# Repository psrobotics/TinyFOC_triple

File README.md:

# TinyFOC_triple

<br> <br>
<br> <br>

* Compact 3 channel brushless motor driver with external encoder
* Supports I2C (AS5600) or AB (TLE5012B) encoders
* Hardwarer CAN, serial, SPI interface
* Input voltage: 9v - 24v, maximum phase current 1.5A
* 4 layer board / FR4 / 1.0mm thickness
* [SimpleFOC](https://github.com/simplefoc) compatible

Design file exported with [Autodesk EAGLE](https://www.autodesk.com/products/eagle/overview?term=1-YEAR&tab=subscription)

## ICs
* MCU [STM32F446RET6](https://www.st.com/en/microcontrollers-microprocessors/stm32f446re.html)
* Motor driver [DRV8313](https://www.ti.com/product/DRV8313?utm_source=google&utm_medium=cpc&utm_campaign=asc-null-null-GPN_EN-cpc-pf-google-wwe&utm_content=DRV8313&ds_k=DRV8313&DCM=yes&gclid=EAIaIQobChMIroSGo5PH_gIV7TatBh0lfQ1tEAAYASAAEgJeRvD_BwE&gclsrc=aw.ds) or [MS8313](https://www.lcsc.com/product-detail/Others_Hangzhou-Ruimeng-Tech-MS8313_C231942.html)
* Encoder [AS5600](https://ams.com/en/as5600) or [TLE5012B E1000](https://www.infineon.com/cms/en/product/sensor/magnetic-sensors/magnetic-position-sensors/angle-sensors/tle5012b-e1000/)

## Pin Out
<br> <br>

## License
MIT License

## Contact
* Shuang Peng, {shuangpe}@usc.edu

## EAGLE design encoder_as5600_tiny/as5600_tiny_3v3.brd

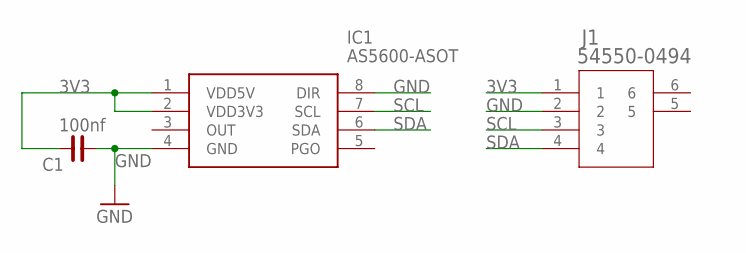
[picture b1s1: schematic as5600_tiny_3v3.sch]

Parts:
C1: 100nf; C0603
IC1: AS5600-ASOT; SOIC127P600X175-8N
J1: 54550-0494; CON4_1X4_DRB2_MOL

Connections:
3V3: C1.2, IC1.1 (VDD5V), IC1.2 (VDD3V3), J1.1
GND: C1.1, IC1.4 (GND), IC1.8 (DIR), J1.2
SCL: IC1.7 (SCL), J1.3
SDA: IC1.6 (SDA), J1.4

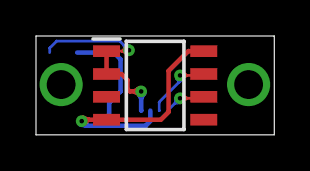
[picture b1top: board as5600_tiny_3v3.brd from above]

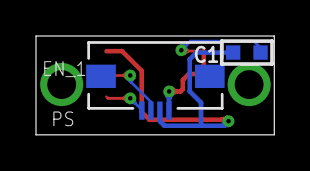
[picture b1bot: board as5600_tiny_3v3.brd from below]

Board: 2 copper layers, 13.2 x 5.5 mm, 3 parts (2 on the bottom side), 4 nets.

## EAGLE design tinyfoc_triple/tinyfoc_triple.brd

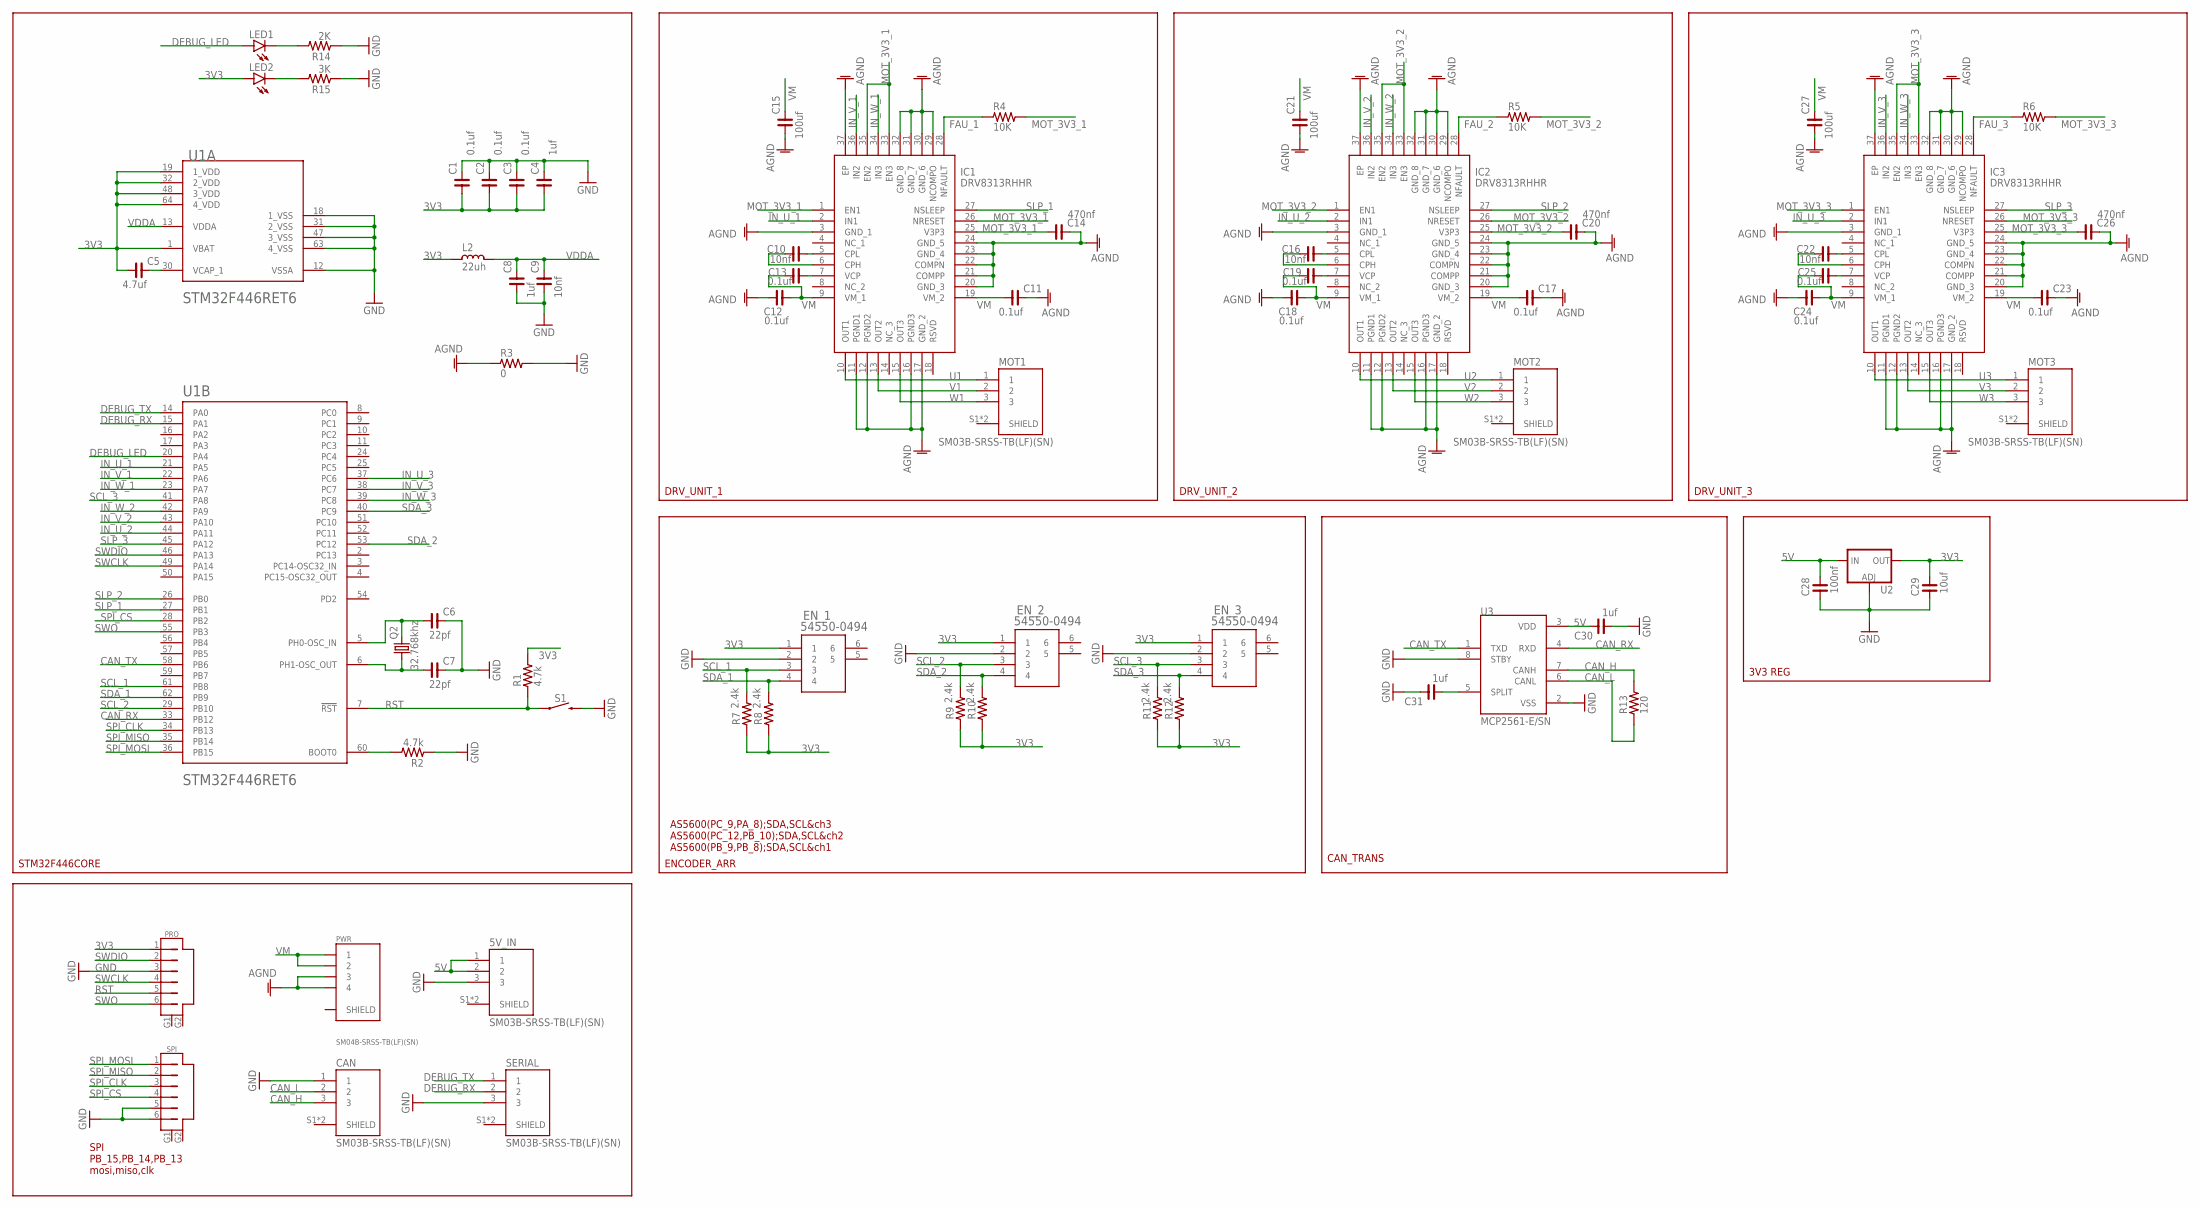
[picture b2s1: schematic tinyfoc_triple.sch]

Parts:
5V_IN: SM03B-SRSS-TB(LF)(SN); JST_SM03B-SRSS-TB(LF)(SN)
C1, C2, C3, C11, C12, C13, C17, C18, C19, C23, C24, C25: 0.1uf; C0603
C4, C8, C30, C31: 1uf; C0603
C5: 4.7uf; C1206
C6, C7: 22pf; C0603
C9, C10, C16, C22: 10nf; C0603
C14, C20, C26: 470nf; C0603
C15, C21, C27: 100uf; C1206
C28: 100nf; C0603
C29: 10uf; C0603
CAN: SM03B-SRSS-TB(LF)(SN); JST_SM03B-SRSS-TB(LF)(SN)
EN_1, EN_2, EN_3: 54550-0494; CON4_1X4_DRB2_MOL
IC1, IC2, IC3: DRV8313RHHR; QFN50P600X600X100-37N
L2: 22uh; PM0603
LED1, LED2: LEDCHIPLED_0603; CHIPLED_0603
MOT1, MOT2, MOT3: SM03B-SRSS-TB(LF)(SN); JST_SM03B-SRSS-TB(LF)(SN)
PRO: SM06B-SRSS-TB; SM06B
PWR: SM04B-SRSS-TB(LF)(SN); JST_SM04B-SRSS-TB(LF)(SN)
Q2: 32.768khz; 3.2X1.5
R1, R2: 4.7k; R0603
R3: 0; R0603
R4, R5, R6: 10K; R0603
R7, R8, R9, R10, R11, R12: 2.4k; R0603
R13: 120; R0603
R14: 2K; R0603
R15: 3K; R0603
S1: MOMENTARY-SWITCH-SPST-SMD-RIGHT-ANGLE; TACTILE_SWITCH_SMD_RIGHT_ANGLE
SERIAL: SM03B-SRSS-TB(LF)(SN); JST_SM03B-SRSS-TB(LF)(SN)
SPI: SM06B-SRSS-TB; SM06B
U1: STMICROELECTRONICS_STM32F446RET6STMICROELECTRONIC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; STMICROELECTRONICS_STM32F446RET6_0
U2: V_REG_LM1117SOT223; SOT223
U3: MCP2561-E/SN; SOIC127P600X175-8N

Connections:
3V3: C1.1, C2.1, C3.1, C4.1, C5.1, C29.2, EN_1.1, EN_2.1, EN_3.1, L2.2, LED2.A, PRO.1, R1.2, R7.1, R8.1, R9.1, R10.1, R11.1, R12.1, U1.1 (VBAT), U1.19 (1_VDD), U1.32 (2_VDD), U1.48 (3_VDD), U1.64 (4_VDD), U2.2 (OUT), U2.4 (OUT)
5V: 5V_IN.1, 5V_IN.2, C28.2, C30.2, U2.3 (IN), U3.3 (VDD)
AGND: C11.2, C12.1, C14.2, C15.1, C17.2, C18.1, C20.2, C21.1, C23.2, C24.1, C26.2, C27.1, IC1.3 (GND_1), IC1.11 (PGND1), IC1.12 (PGND2), IC1.16 (PGND3), IC1.17 (GND_2), IC1.20 (GND_3), IC1.21 (COMPP), IC1.22 (COMPN), IC1.23 (GND_4), IC1.24 (GND_5), IC1.29 (NCOMPO), IC1.30 (GND_6), IC1.31 (GND_7), IC1.32 (GND_8), IC1.37 (EP), IC2.3 (GND_1), IC2.11 (PGND1), IC2.12 (PGND2), IC2.16 (PGND3), IC2.17 (GND_2), IC2.20 (GND_3), IC2.21 (COMPP), IC2.22 (COMPN), IC2.23 (GND_4), IC2.24 (GND_5), IC2.29 (NCOMPO), IC2.30 (GND_6), IC2.31 (GND_7), IC2.32 (GND_8), IC2.37 (EP), IC3.3 (GND_1), IC3.11 (PGND1), IC3.12 (PGND2), IC3.16 (PGND3), IC3.17 (GND_2), IC3.20 (GND_3), IC3.21 (COMPP), IC3.22 (COMPN), IC3.23 (GND_4), IC3.24 (GND_5), IC3.29 (NCOMPO), IC3.30 (GND_6), IC3.31 (GND_7), IC3.32 (GND_8), IC3.37 (EP), PWR.3, PWR.4, R3.1
CAN_H: CAN.3, R13.2, U3.7 (CANH)
CAN_L: CAN.2, R13.1, U3.6 (CANL)
CAN_RX: U1.33 (PB12), U3.4 (RXD)
CAN_TX: U1.58 (PB6), U3.1 (TXD)
DEBUG_LED: LED1.A, U1.20 (PA4)
DEBUG_RX: SERIAL.2, U1.15 (PA1)
DEBUG_TX: SERIAL.1, U1.14 (PA0)
FAU_1: IC1.28 (NFAULT), R4.1
FAU_2: IC2.28 (NFAULT), R5.1
FAU_3: IC3.28 (NFAULT), R6.1
GND: 5V_IN.3, C1.2, C2.2, C3.2, C4.2, C6.2, C7.2, C8.1, C9.1, C28.1, C29.1, C30.1, C31.2, CAN.1, EN_1.2, EN_2.2, EN_3.2, PRO.3, R2.1, R3.2, R14.1, R15.1, S1.2, SERIAL.3, SPI.5, SPI.6, U1.12 (VSSA), U1.18 (1_VSS), U1.31 (2_VSS), U1.47 (3_VSS), U1.63 (4_VSS), U2.1 (ADJ), U3.2 (VSS), U3.8 (STBY)
IN_U_1: IC1.2 (IN1), U1.21 (PA5)
IN_U_2: IC2.2 (IN1), U1.44 (PA11)
IN_U_3: IC3.2 (IN1), U1.37 (PC6)
IN_V_1: IC1.36 (IN2), U1.22 (PA6)
IN_V_2: IC2.36 (IN2), U1.43 (PA10)
IN_V_3: IC3.36 (IN2), U1.38 (PC7)
IN_W_1: IC1.34 (IN3), U1.23 (PA7)
IN_W_2: IC2.34 (IN3), U1.42 (PA9)
IN_W_3: IC3.34 (IN3), U1.39 (PC8)
MOT_3V3_1: C14.1, IC1.1 (EN1), IC1.25 (V3P3), IC1.26 (NRESET), IC1.33 (EN3), IC1.35 (EN2), R4.2
MOT_3V3_2: C20.1, IC2.1 (EN1), IC2.25 (V3P3), IC2.26 (NRESET), IC2.33 (EN3), IC2.35 (EN2), R5.2
MOT_3V3_3: C26.1, IC3.1 (EN1), IC3.25 (V3P3), IC3.26 (NRESET), IC3.33 (EN3), IC3.35 (EN2), R6.2
unnamed: C5.2, U1.30 (VCAP_1)
unnamed: R2.2, U1.60 (BOOT0)
unnamed: C7.1, Q2.1, U1.6 (PH1-OSC_OUT)
unnamed: C10.2, IC1.5 (CPL)
unnamed: C6.1, Q2.2, U1.5 (PH0-OSC_IN)
unnamed: C10.1, IC1.6 (CPH)
unnamed: C13.2, IC1.7 (VCP)
unnamed: C16.2, IC2.5 (CPL)
unnamed: C16.1, IC2.6 (CPH)
unnamed: C19.2, IC2.7 (VCP)
unnamed: C22.2, IC3.5 (CPL)
unnamed: C22.1, IC3.6 (CPH)
unnamed: C25.2, IC3.7 (VCP)
unnamed: C31.1, U3.5 (SPLIT)
unnamed: LED2.C, R15.2
unnamed: LED1.C, R14.2
RST: PRO.5, R1.1, S1.1, U1.7 (!RST!)
SCL_1: EN_1.3, R7.2, U1.61 (PB8)
SCL_2: EN_2.3, R9.2, U1.29 (PB10)
SCL_3: EN_3.3, R11.2, U1.41 (PA8)
SDA_1: EN_1.4, R8.2, U1.62 (PB9)
SDA_2: EN_2.4, R10.2, U1.53 (PC12)
SDA_3: EN_3.4, R12.2, U1.40 (PC9)
SLP_1: IC1.27 (NSLEEP), U1.27 (PB1)
SLP_2: IC2.27 (NSLEEP), U1.26 (PB0)
SLP_3: IC3.27 (NSLEEP), U1.45 (PA12)
SPI_CLK: SPI.3, U1.34 (PB13)
SPI_CS: SPI.4, U1.28 (PB2)
SPI_MISO: SPI.2, U1.35 (PB14)
SPI_MOSI: SPI.1, U1.36 (PB15)
SWCLK: PRO.4, U1.49 (PA14)
SWDIO: PRO.2, U1.46 (PA13)
SWO: PRO.6, U1.55 (PB3)
U1: IC1.10 (OUT1), MOT1.1
U2: IC2.10 (OUT1), MOT2.1
U3: IC3.10 (OUT1), MOT3.1
V1: IC1.13 (OUT2), MOT1.2
V2: IC2.13 (OUT2), MOT2.2
V3: IC3.13 (OUT2), MOT3.2
VDDA: C8.2, C9.2, L2.1, U1.13 (VDDA)
VM: C11.1, C12.2, C13.1, C15.2, C17.1, C18.2, C19.1, C21.2, C23.1, C24.2, C25.1, C27.2, IC1.9 (VM_1), IC1.19 (VM_2), IC2.9 (VM_1), IC2.19 (VM_2), IC3.9 (VM_1), IC3.19 (VM_2), PWR.1, PWR.2
W1: IC1.15 (OUT3), MOT1.3
W2: IC2.15 (OUT3), MOT2.3
W3: IC3.15 (OUT3), MOT3.3

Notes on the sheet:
STM32F446CORE
DRV_UNIT_1
DRV_UNIT_2
DRV_UNIT_3
ENCODER_ARR
AS5600(PC_9,PA_8);SDA,SCL&ch3 AS5600(PC_12,PB_10);SDA,SCL&ch2 AS5600(PB_9,PB_8);SDA,SCL&ch1
SPI PB_15,PB_14,PB_13 mosi,miso,clk
3V3 REG
CAN_TRANS

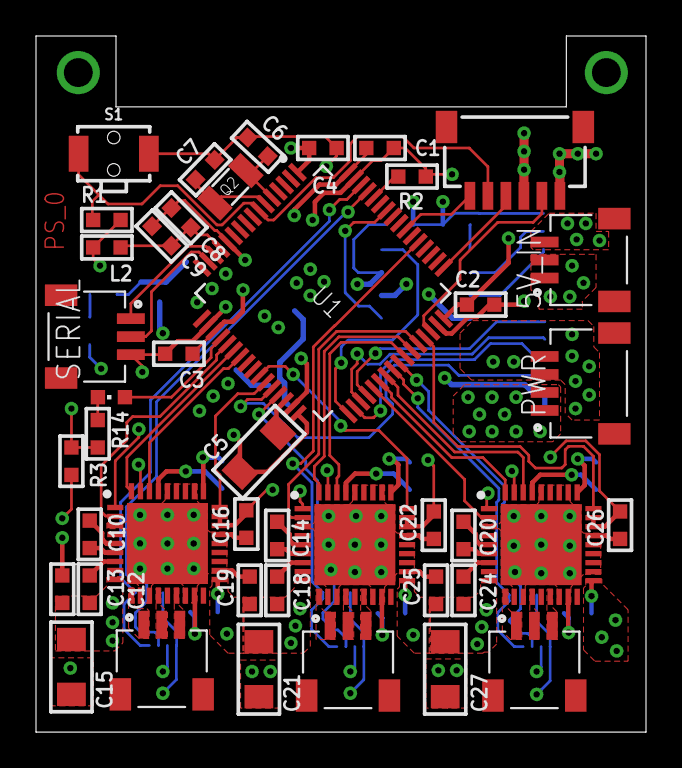
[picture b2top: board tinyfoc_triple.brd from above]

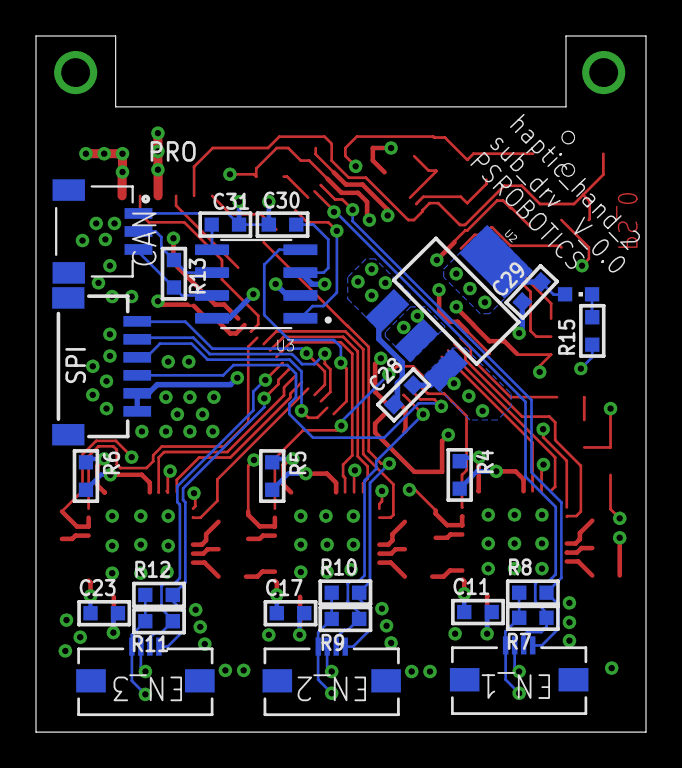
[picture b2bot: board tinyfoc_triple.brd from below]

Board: 4 copper layers, 33.9 x 38.7 mm, 69 parts (26 on the bottom side), 70 nets.

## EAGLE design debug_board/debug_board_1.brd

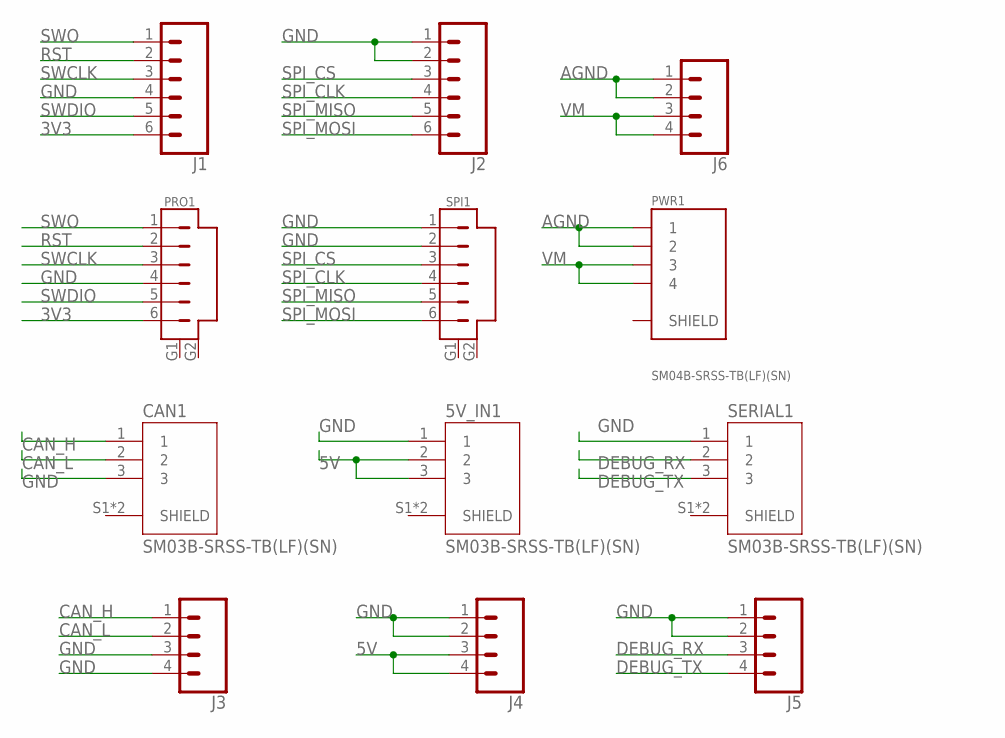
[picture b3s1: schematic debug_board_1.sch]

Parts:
5V_IN1: SM03B-SRSS-TB(LF)(SN); JST_SM03B-SRSS-TB(LF)(SN)
CAN1: SM03B-SRSS-TB(LF)(SN); JST_SM03B-SRSS-TB(LF)(SN)
J1, J2: CONN_06LONGPADS; 1X06_LONGPADS
J3, J4, J5, J6: CONN_04LONGPADS; 1X04_LONGPADS
PRO1: SM06B-SRSS-TB; SM06B
PWR1: SM04B-SRSS-TB(LF)(SN); JST_SM04B-SRSS-TB(LF)(SN)
SERIAL1: SM03B-SRSS-TB(LF)(SN); JST_SM03B-SRSS-TB(LF)(SN)
SPI1: SM06B-SRSS-TB; SM06B

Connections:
3V3: J1.6, PRO1.6
5V: 5V_IN1.2, 5V_IN1.3, J4.3, J4.4
AGND: J6.1, J6.2, PWR1.1, PWR1.2
CAN_H: CAN1.1, J3.1
CAN_L: CAN1.2, J3.2
DEBUG_RX: J5.3, SERIAL1.2
DEBUG_TX: J5.4, SERIAL1.3
GND: 5V_IN1.1, CAN1.3, J1.4, J2.1, J2.2, J3.3, J3.4, J4.1, J4.2, J5.1, J5.2, PRO1.4, SERIAL1.1, SPI1.1, SPI1.2
RST: J1.2, PRO1.2
SPI_CLK: J2.4, SPI1.4
SPI_CS: J2.3, SPI1.3
SPI_MISO: J2.5, SPI1.5
SPI_MOSI: J2.6, SPI1.6
SWCLK: J1.3, PRO1.3
SWDIO: J1.5, PRO1.5
SWO: J1.1, PRO1.1
VM: J6.3, J6.4, PWR1.3, PWR1.4

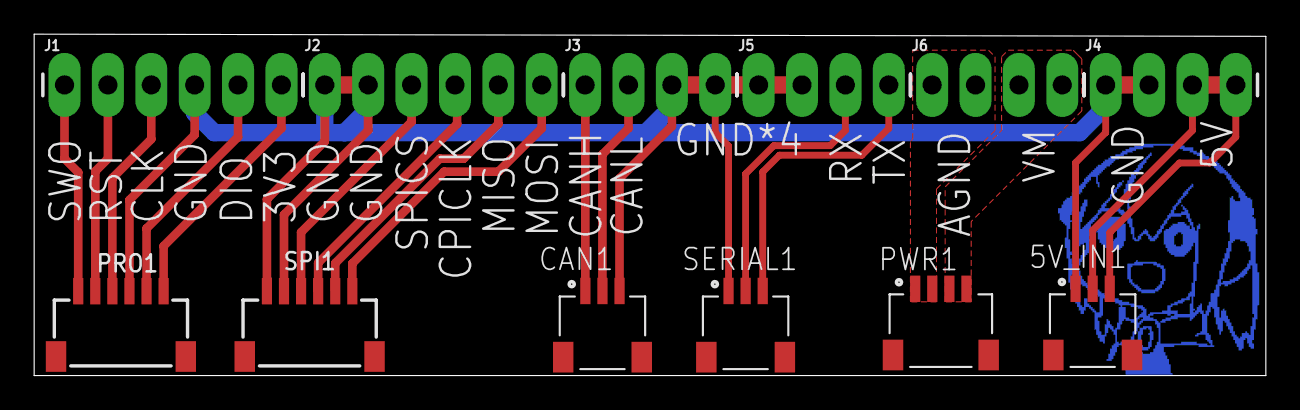
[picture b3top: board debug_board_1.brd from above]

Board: 2 copper layers, 72.1 x 20.0 mm, 13 parts (0 on the bottom side), 17 nets.

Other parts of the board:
U$1: SODAYO_1

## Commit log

2023-04-26 init: 0426
2023-04-26 add: 0426

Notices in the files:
parts and their libraries:
SparkFun-Connectors: Licensing: Creative Commons ShareAlike 4.0 International - https://creativecommons.org/licenses/by-sa/4.0
rc-master-smd: Copyright (C) 2007, Bob Starr
crystal-geyer_V1_0: Copyright: Geyer-Electronic
